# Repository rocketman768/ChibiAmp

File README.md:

# QRPAmp

A complete 10W amp for the HF bands.

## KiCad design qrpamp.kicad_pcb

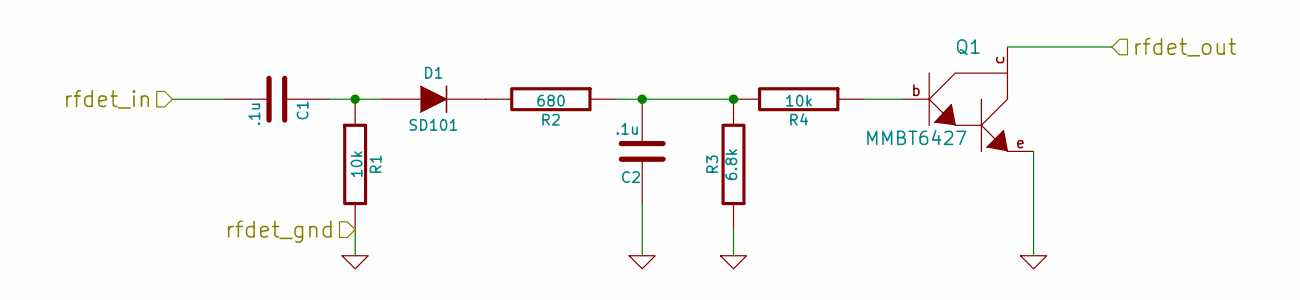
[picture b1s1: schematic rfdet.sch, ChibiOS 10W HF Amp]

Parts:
C1, C2: .1u; C_0805_HandSoldering
D1: SD101; SOD-123
Q1: MMBT6427; SOT-23-EBC_HandSoldering
R1, R4: 10k; R_1206_HandSoldering
R2: 680; R_1206_HandSoldering
R3: 6.8k; R_1206_HandSoldering

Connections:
/Microcontroller/mcu_rfdet: Q1.c; also elsewhere on the board
/RF In/Out/raw_input: C1.2; also elsewhere on the board
GND: C2.1, Q1.e, R1.2, R3.1; also elsewhere on the board
unnamed: C1.1, D1.1 (A), R1.1
unnamed: C2.2, R2.1, R3.2, R4.2
unnamed: D1.2 (K), R2.2
unnamed: Q1.b, R4.1

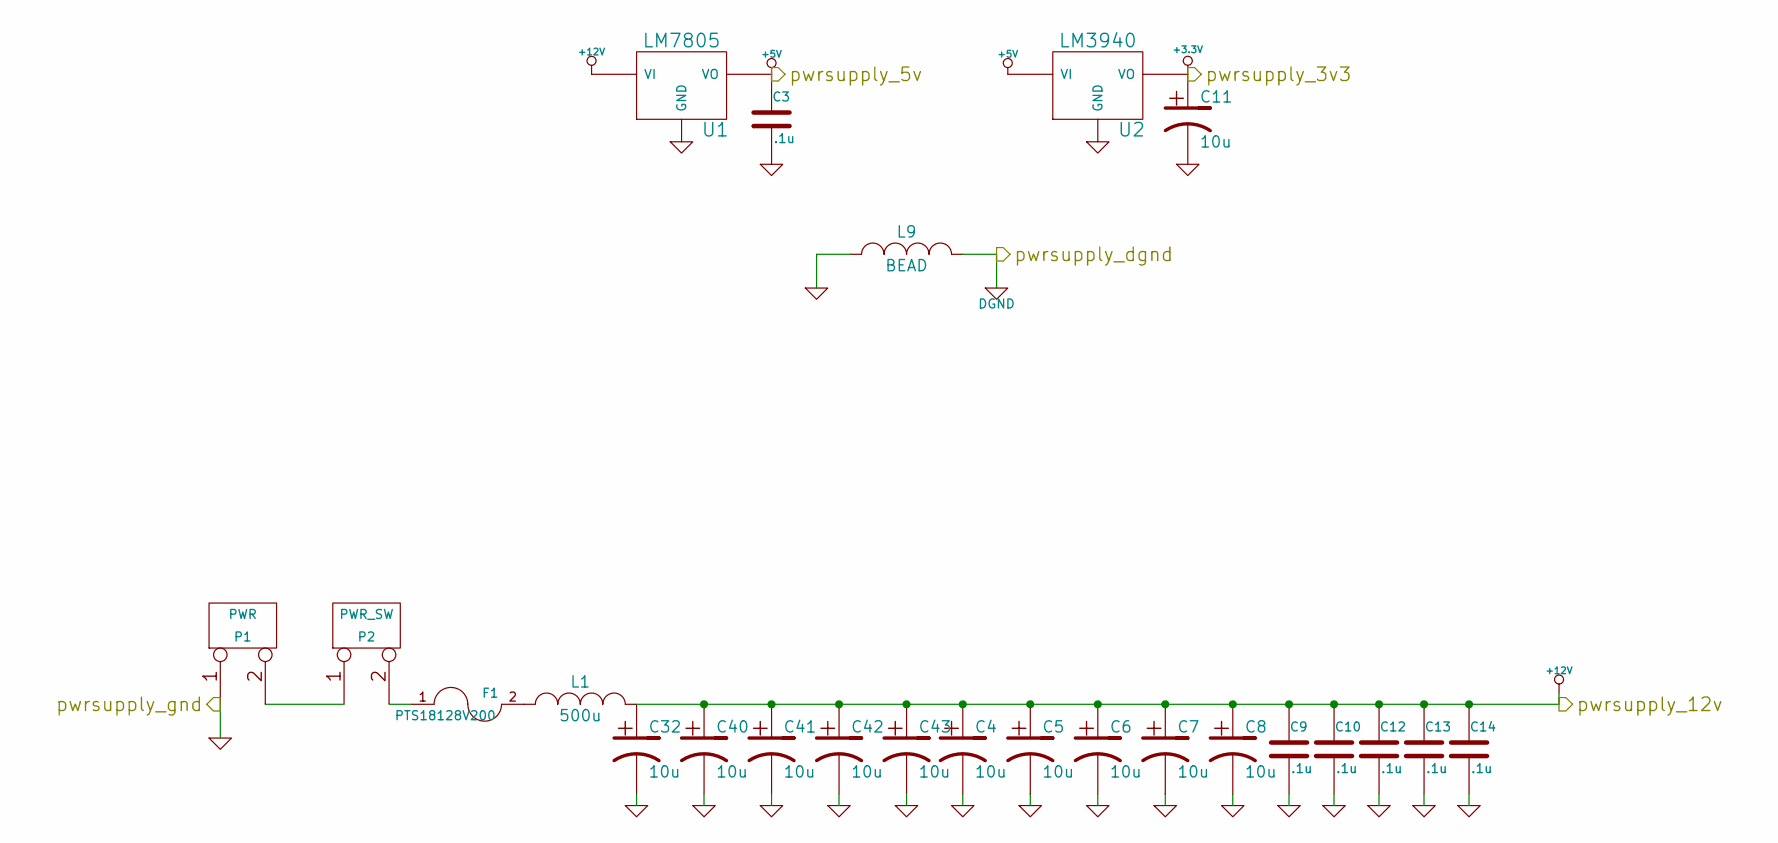
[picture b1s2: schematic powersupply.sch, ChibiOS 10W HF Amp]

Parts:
C3, C9, C10, C12, C13, C14: .1u; C_0805_HandSoldering
C4, C5, C6, C7, C8, C32, C40, C41, C42, C43: 10u; C_Radial_D5_L11_P2.5
C11: 10u; Capacitor5x11RM2.5
F1: PTS18128V200; SMD-1812_l
L1: 500u; TOROID-50
L9: BEAD; WE-SUCKW
P1: PWR; PWR2-16AWG
P2: PWR_SW; PWR2-16AWG
U1: LM7805; DPAK-3_VIVOGND
U2: LM3940; SOT-223

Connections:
+3.3V: C11.1, U2.VO; also elsewhere on the board
+5V: C3.1, U1.VO, U2.VI; also elsewhere on the board
+12V: C4.1, C5.1, C6.1, C7.1, C8.1, C9.1, C10.1, C12.1, C13.1, C14.1, C32.1, C40.1, C41.1, C42.1, C43.1, L1.2, U1.VI; also elsewhere on the board
DGND: L9.2; also elsewhere on the board
GND: C3.2, C4.2, C5.2, C6.2, C7.2, C8.2, C9.2, C10.2, C11.2, C12.2, C13.2, C14.2, C32.2, C40.2, C41.2, C42.2, C43.2, L9.1, P1.1, U1.GND, U2.GND; also elsewhere on the board
unnamed: F1.1, P2.2 (PM)
unnamed: F1.2, L1.1
unnamed: P1.2 (PM), P2.1

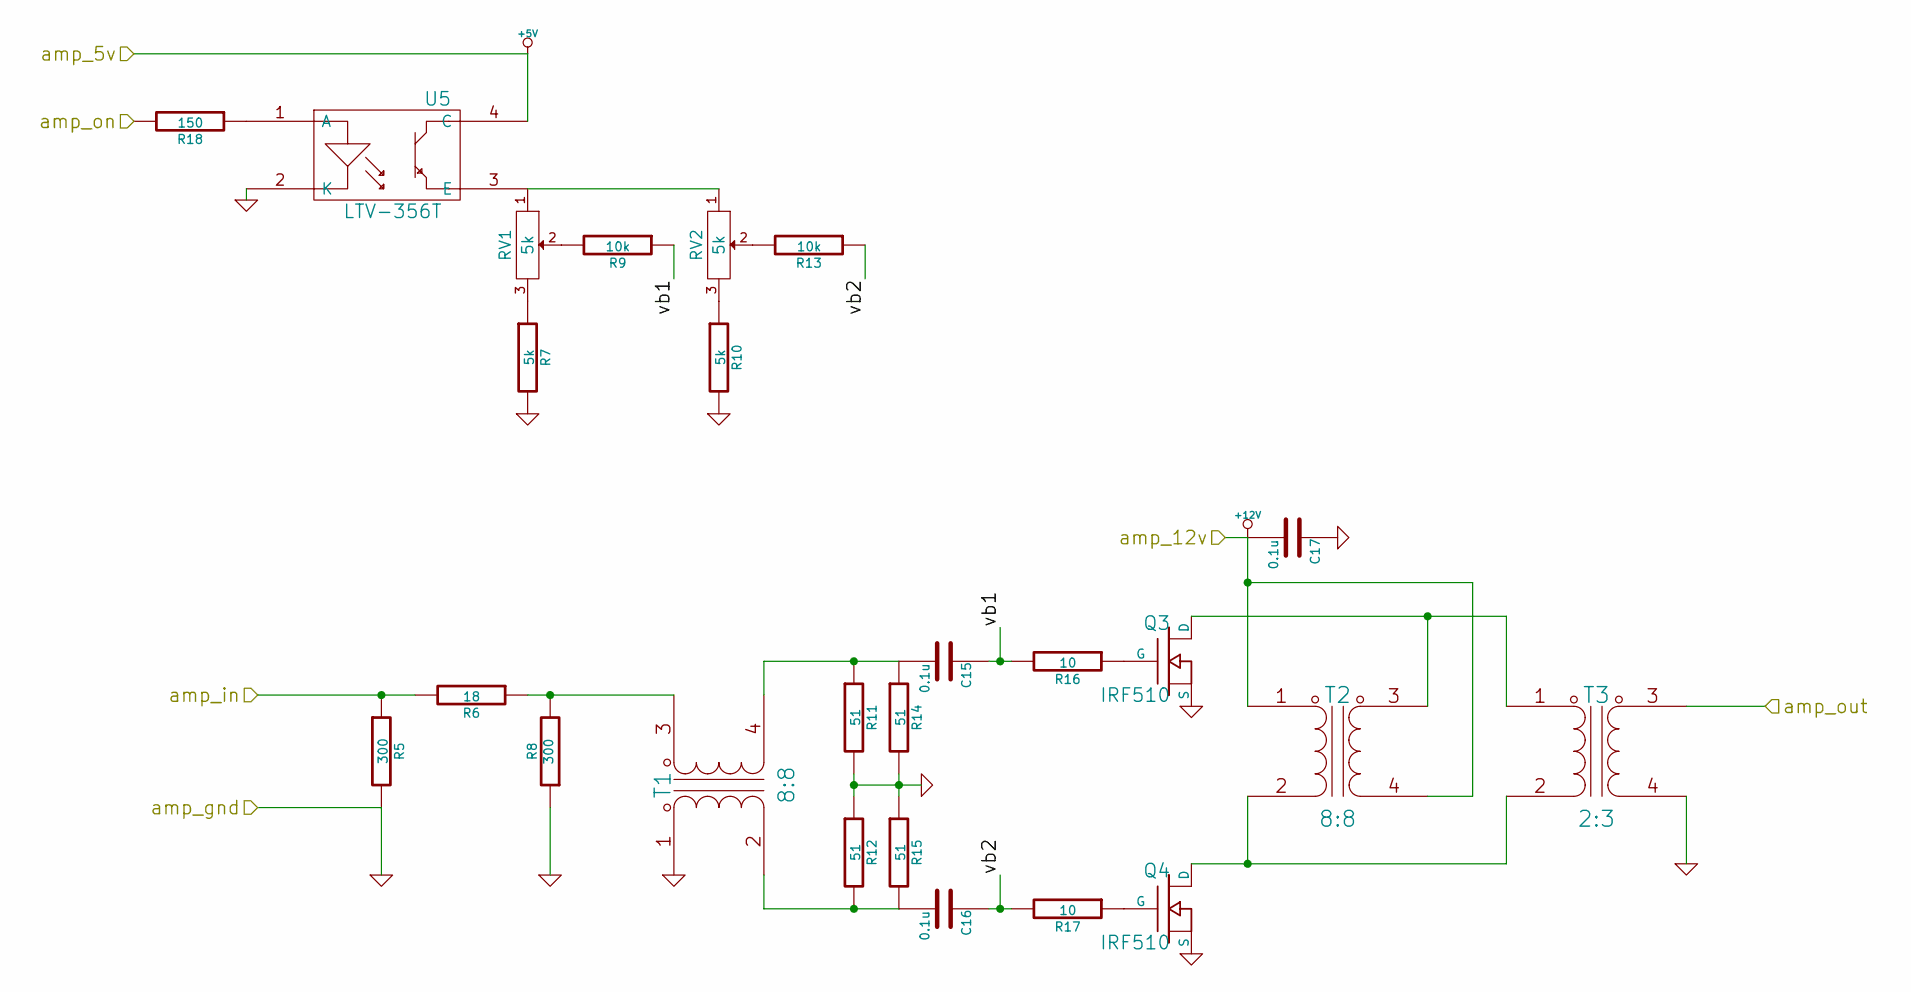
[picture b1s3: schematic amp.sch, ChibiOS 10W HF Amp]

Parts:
C15, C16, C17: 0.1u; C_0805_HandSoldering
Q3, Q4: IRF510; TO-220_FET-GDS_Horizontal_MountedFromLS_LargePads
R5, R8: 300; R1
R6: 18; R1
R7, R10: 5k; R_1206_HandSoldering
R9, R13: 10k; R_1206_HandSoldering
R11, R12, R14, R15: 51; R1
R16, R17: 10; R_1206_HandSoldering
R18: 150; R_1206_HandSoldering
RV1, RV2: 5k; Potentiometer_Trimmer_Piher_PT10_H01
T1, T2: 8:8; BN2-202
T3: 2:3; BN2-3312
U5: LTV-356T; Optocoupler_SMD_HandSoldering_KPC357_LTV35x_PC357_SingleCha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

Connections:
+5V: U5.4 (C); also elsewhere on the board
+12V: C17.2, T2.1 (PA), T2.4 (SB); also elsewhere on the board
/Amplifier/amp_in: R5.1, R6.2; also elsewhere on the board
/Amplifier/amp_on: R18.2; also elsewhere on the board
/Amplifier/amp_out: T3.3 (SA); also elsewhere on the board
/Amplifier/vb1: C15.1, R9.1, R16.2
/Amplifier/vb2: C16.1, R13.1, R17.2
GND: C17.1, Q3.S, Q4.S, R5.2, R7.2, R8.1, R10.2, R11.2, R12.1, R14.2, R15.1, T1.1 (PA), T3.4 (SB), U5.2 (K); also elsewhere on the board
unnamed: C15.2, R11.1, R14.1, T1.4 (SB)
unnamed: C16.2, R12.2, R15.2, T1.2 (PB)
unnamed: Q3.D, T2.3 (SA), T3.1 (PA)
unnamed: Q3.G, R16.1
unnamed: Q4.D, T2.2 (PB), T3.2 (PB)
unnamed: Q4.G, R17.1
unnamed: R6.1, R8.2, T1.3 (SA)
unnamed: R7.1, RV1.3
unnamed: R9.2, RV1.2
unnamed: R10.1, RV2.3
unnamed: R13.2, RV2.2
unnamed: R18.1, U5.1 (A)
unnamed: RV1.1, RV2.1, U5.3 (E)

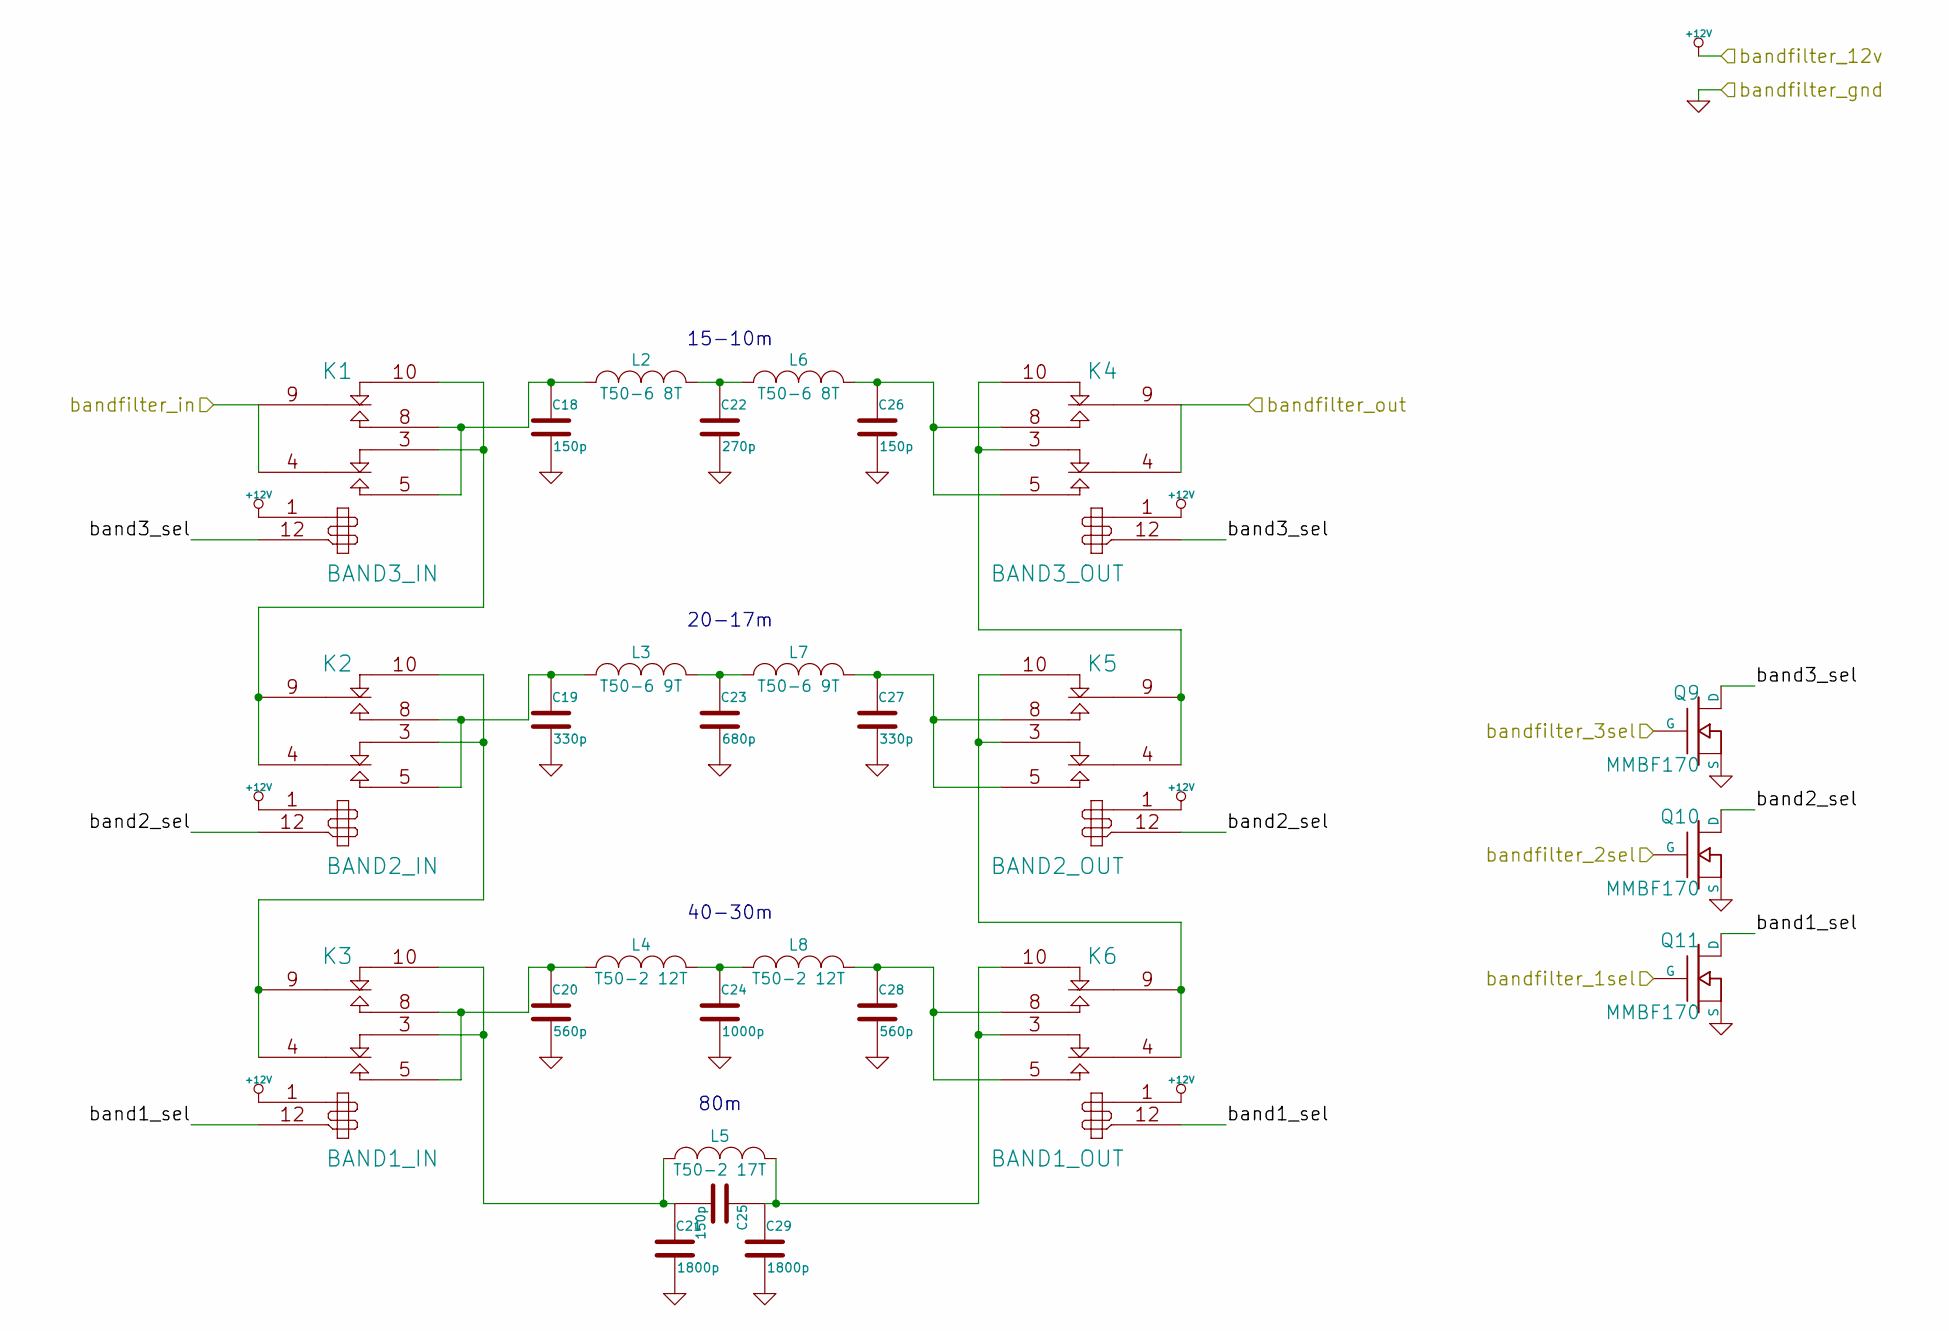
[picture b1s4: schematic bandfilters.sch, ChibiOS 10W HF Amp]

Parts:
C18, C25, C26: 150p; C1
C19, C27: 330p; C1
C20, C28: 560p; C1
C21, C29: 1800p; C1
C22: 270p; C1
C23: 680p; C1
C24: 1000p; C1
K1: BAND3_IN; EC2-12NU
K2: BAND2_IN; EC2-12NU
K3: BAND1_IN; EC2-12NU
K4: BAND3_OUT; EC2-12NU
K5: BAND2_OUT; EC2-12NU
K6: BAND1_OUT; EC2-12NU
L2, L6: T50-6 8T; TOROID-50
L3, L7: T50-6 9T; TOROID-50
L4, L8: T50-2 12T; TOROID-50
L5: T50-2 17T; TOROID-50
Q9, Q10, Q11: MMBF170; SOT-23-DGS_HandSoldering

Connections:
+12V: K1.1, K2.1, K3.1, K4.1, K5.1, K6.1; also elsewhere on the board
/Amplifier/amp_out: K1.4, K1.9; also elsewhere on the board
/Band Filters/band1_sel: K3.12, K6.12, Q11.D
/Band Filters/band2_sel: K2.12, K5.12, Q10.D
/Band Filters/band3_sel: K1.12, K4.12, Q9.D
/Band Filters/bandfilter_1sel: Q11.G; also elsewhere on the board
/Band Filters/bandfilter_2sel: Q10.G; also elsewhere on the board
/Band Filters/bandfilter_3sel: Q9.G; also elsewhere on the board
/Band Filters/bandfilter_out: K4.4, K4.9; also elsewhere on the board
GND: C18.2, C19.2, C20.2, C21.2, C22.2, C23.2, C24.2, C26.2, C27.2, C28.2, C29.2, Q9.S, Q10.S, Q11.S; also elsewhere on the board
unnamed: C18.1, K1.5, K1.8, L2.1
unnamed: C19.1, K2.5, K2.8, L3.1
unnamed: C20.1, K3.5, K3.8, L4.1
unnamed: C21.1, C25.2, K3.3 (R1), K3.10, L5.1
unnamed: C22.1, L2.2, L6.1
unnamed: C23.1, L3.2, L7.1
unnamed: C24.1, L4.2, L8.1
unnamed: C25.1, C29.1, K6.3 (R1), K6.10, L5.2
unnamed: C26.1, K4.5, K4.8, L6.2
unnamed: C27.1, K5.5, K5.8, L7.2
unnamed: C28.1, K6.5, K6.8, L8.2
unnamed: K1.3 (R1), K1.10, K2.4, K2.9
unnamed: K2.3 (R1), K2.10, K3.4, K3.9
unnamed: K4.3 (R1), K4.10, K5.4, K5.9
unnamed: K5.3 (R1), K5.10, K6.4, K6.9

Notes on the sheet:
80m
40-30m
20-17m
15-10m

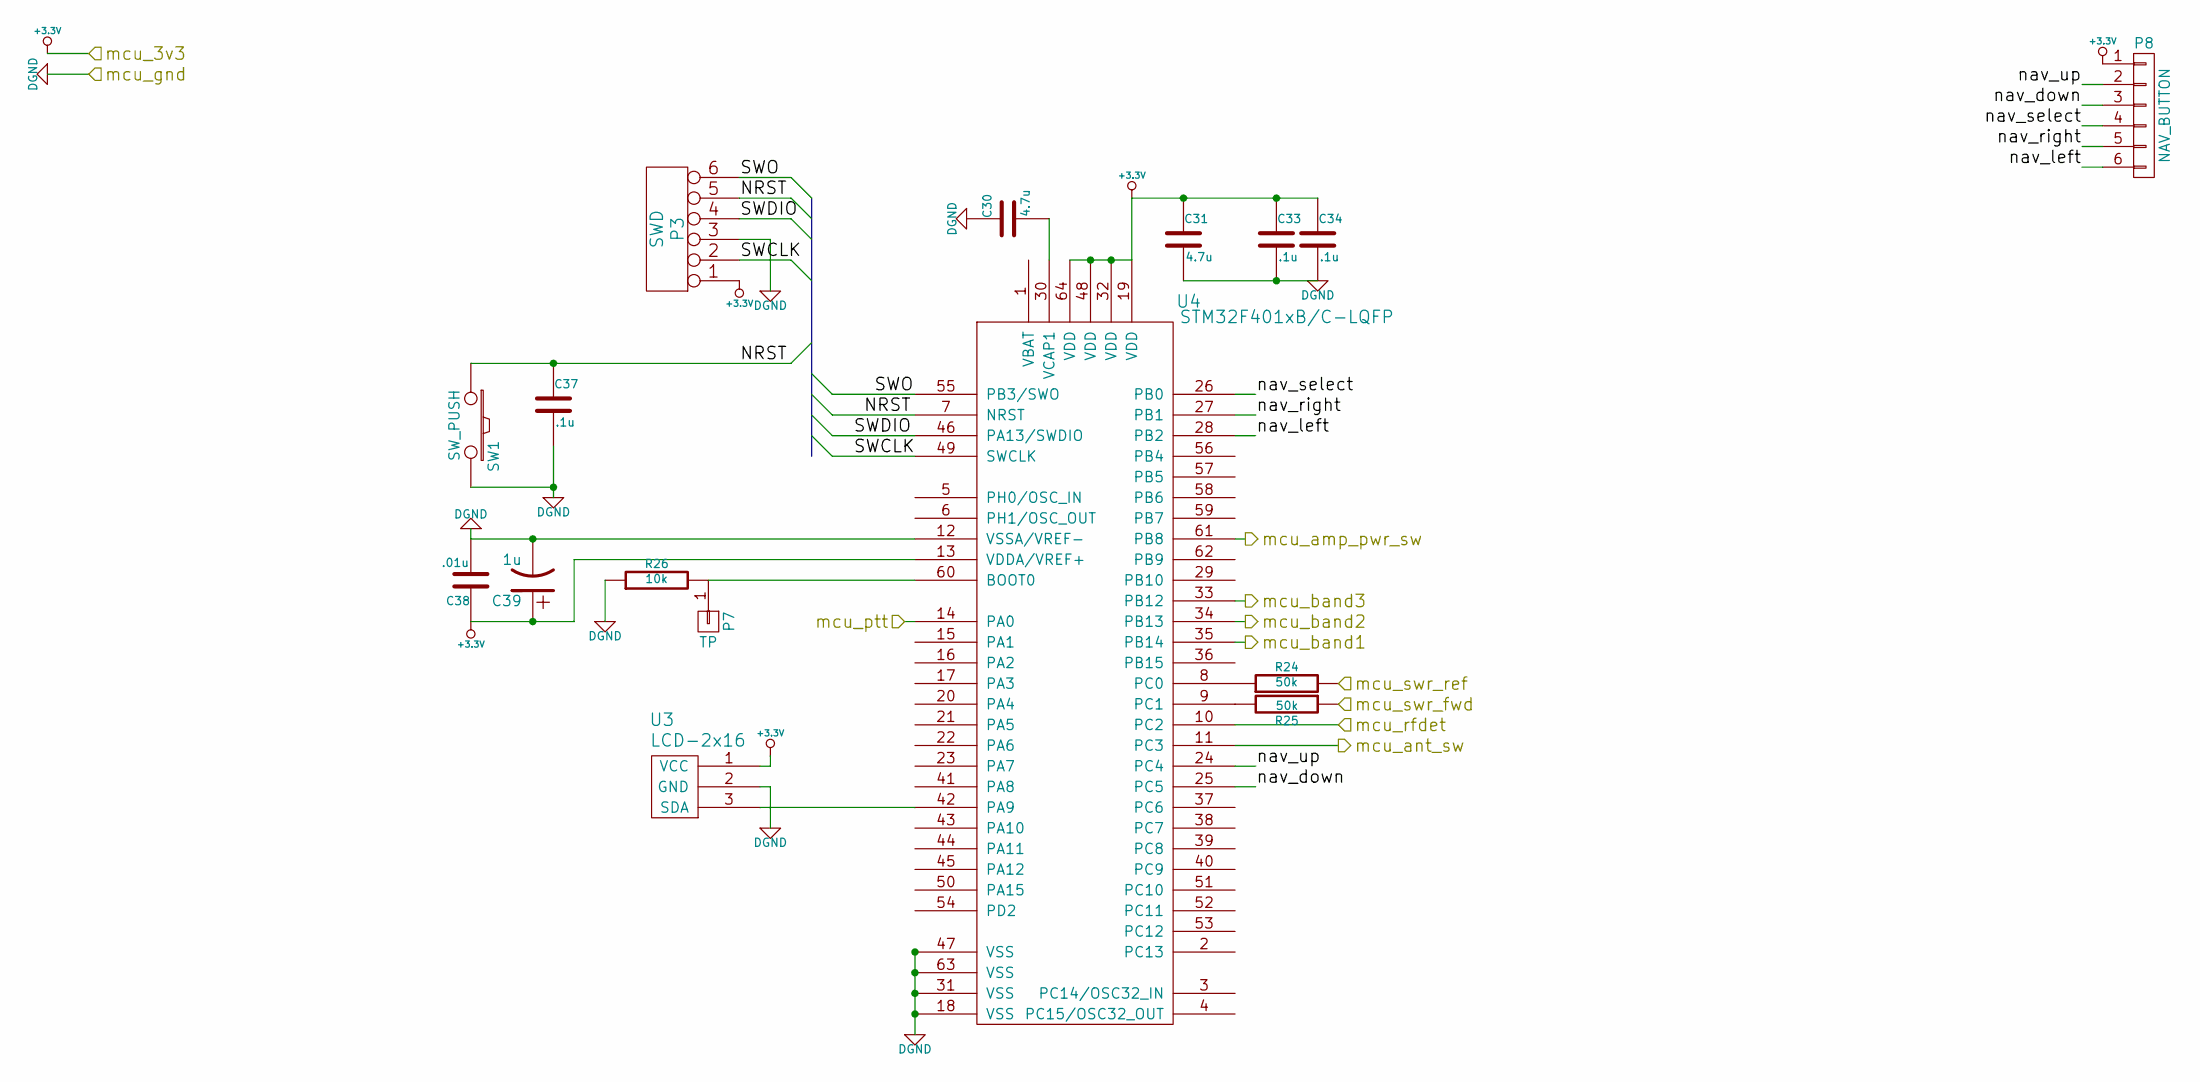
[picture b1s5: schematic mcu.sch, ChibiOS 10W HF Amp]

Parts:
C30, C31: 4.7u; C_0805_HandSoldering
C33, C34, C37: .1u; C_0805_HandSoldering
C38: .01u; C_0805_HandSoldering
C39: 1u; C_0805_HandSoldering
P3: SWD; Pin_Header_Straight_1x06
P7: TP; Measurement_Point_Round-SMD-Pad_Small
P8: NAV_BUTTON; Pin_Header_Straight_1x06
R24, R25: 50k; R_1206_HandSoldering
R26: 10k; R_1206_HandSoldering
SW1: SW_PUSH; Pin_Header_Straight_1x02
U3: LCD-2x16; Pin_Header_Straight_1x03
U4: STM32F401xB/C-LQFP; LQFP64

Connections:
+3.3V: C31.1, C33.1, C34.1, C38.1, C39.1, P3.1, P8.1, U3.1 (VCC), U4.13 (VDDA/VREF+), U4.19 (VDD), U4.32 (VDD), U4.48 (VDD), U4.64 (VDD); also elsewhere on the board
/Amplifier/amp_on: U4.61 (PB8); also elsewhere on the board
/Band Filters/bandfilter_1sel: U4.35 (PB14); also elsewhere on the board
/Band Filters/bandfilter_2sel: U4.34 (PB13); also elsewhere on the board
/Band Filters/bandfilter_3sel: U4.33 (PB12); also elsewhere on the board
/Microcontroller/NRST: C37.1, P3.5, SW1.1, U4.7 (NRST)
/Microcontroller/SWCLK: P3.2, U4.49 (SWCLK)
/Microcontroller/SWDIO: P3.4, U4.46 (PA13/SWDIO)
/Microcontroller/SWO: P3.6, U4.55 (PB3/SWO)
/Microcontroller/mcu_ptt: U4.14 (PA0); also elsewhere on the board
/Microcontroller/mcu_rfdet: U4.10 (PC2); also elsewhere on the board
/Microcontroller/mcu_swr_fwd: R25.1; also elsewhere on the board
/Microcontroller/mcu_swr_ref: R24.2; also elsewhere on the board
/Microcontroller/nav_down: P8.3, U4.25 (PC5)
/Microcontroller/nav_left: P8.6, U4.28 (PB2)
/Microcontroller/nav_right: P8.5, U4.27 (PB1)
/Microcontroller/nav_select: P8.4, U4.26 (PB0)
/Microcontroller/nav_up: P8.2, U4.24 (PC4)
/RF In/Out/ant_sw_rly: U4.11 (PC3); also elsewhere on the board
DGND: C30.1, C31.2, C33.2, C34.2, C37.2, C38.2, C39.2, P3.3, R26.1, SW1.2, U3.2 (GND), U4.12 (VSSA/VREF-), U4.18 (VSS), U4.31 (VSS), U4.47 (VSS), U4.63 (VSS); also elsewhere on the board
unnamed: C30.2, U4.30 (VCAP1)
unnamed: P7.1, R26.2, U4.60 (BOOT0)
unnamed: R24.1, U4.8 (PC0)
unnamed: R25.2, U4.9 (PC1)
unnamed: U3.3 (SDA), U4.42 (PA9)

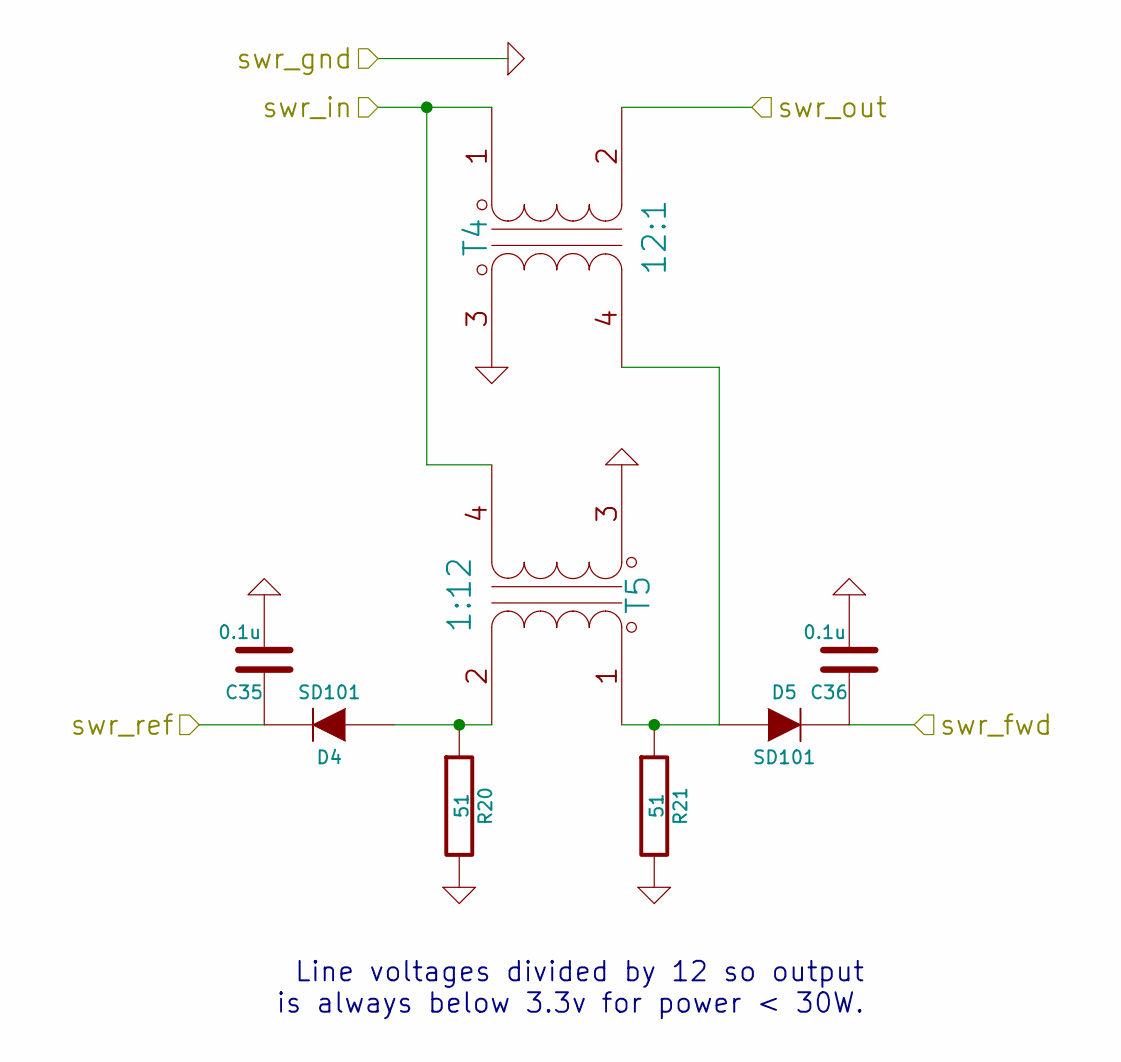
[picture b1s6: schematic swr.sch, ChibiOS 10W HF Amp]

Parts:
C35, C36: 0.1u; C_0805_HandSoldering
D4, D5: SD101; SOD-123
R20, R21: 51; R_1206_HandSoldering
T4: 12:1; TOROID2-50-singleturn
T5: 1:12; TOROID2-50-singleturn

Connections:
/Band Filters/bandfilter_out: T4.1 (PA), T5.4 (SB); also elsewhere on the board
/Microcontroller/mcu_swr_fwd: C36.1, D5.2 (K); also elsewhere on the board
/Microcontroller/mcu_swr_ref: C35.1, D4.2 (K); also elsewhere on the board
/RF In/Out/from_final: T4.2 (PB); also elsewhere on the board
GND: C35.2, C36.2, R20.2, R21.2, T4.3 (SA), T5.3 (SA); also elsewhere on the board
unnamed: D4.1 (A), R20.1, T5.2 (PB)
unnamed: D5.1 (A), R21.1, T4.4 (SB), T5.1 (PA)

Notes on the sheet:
Line voltages divided by 12 so output is always below 3.3v for power < 30W.

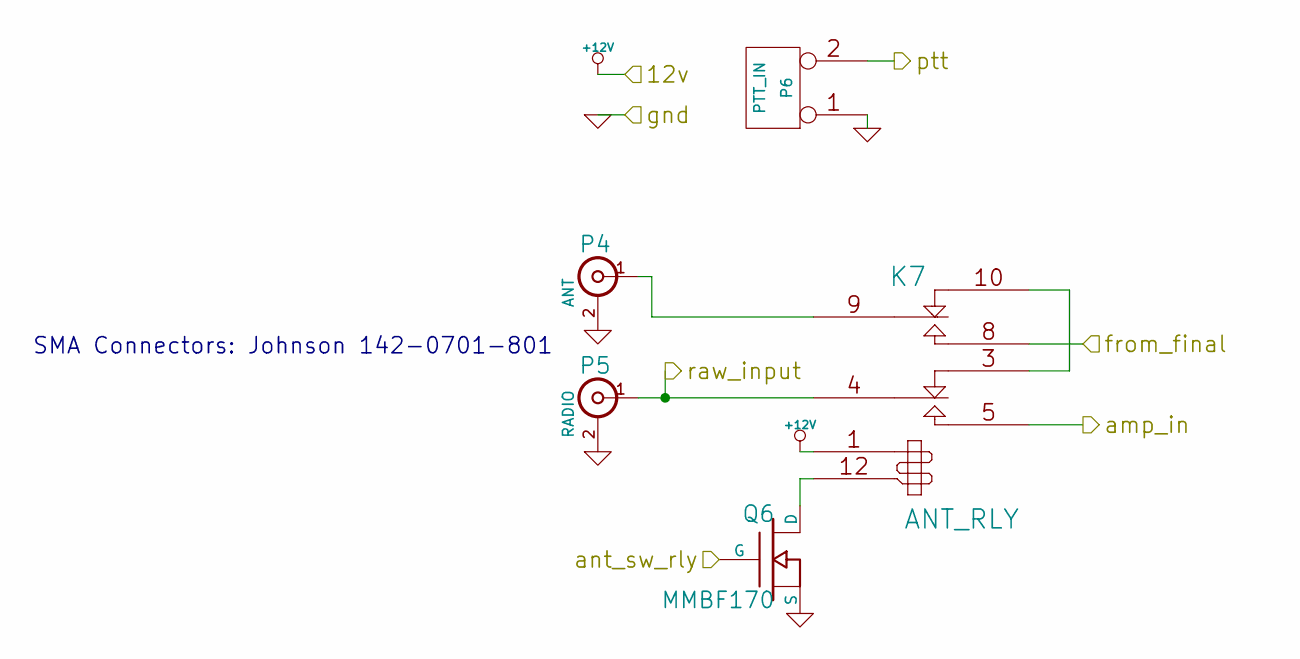
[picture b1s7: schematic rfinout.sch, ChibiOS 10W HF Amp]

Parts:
K7: ANT_RLY; EC2-12NU
P4: ANT; SMA-EDGE-0.375in
P5: RADIO; SMA-EDGE-0.375in
P6: PTT_IN; 3.5MM_SWITCHCRAFT-35RASMT2AHNTRX
Q6: MMBF170; SOT-23-DGS_HandSoldering

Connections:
+12V: K7.1; also elsewhere on the board
/Amplifier/amp_in: K7.5; also elsewhere on the board
/Microcontroller/mcu_ptt: P6.2 (PM); also elsewhere on the board
/RF In/Out/ant_sw_rly: Q6.G; also elsewhere on the board
/RF In/Out/from_final: K7.8; also elsewhere on the board
/RF In/Out/raw_input: K7.4, P5.1 (In); also elsewhere on the board
GND: P4.2 (Ext), P5.2 (Ext), P6.1, Q6.S; also elsewhere on the board
unnamed: K7.9, P4.1 (In)
unnamed: K7.3 (R1), K7.10
unnamed: K7.12, Q6.D

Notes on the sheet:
SMA Connectors: Johnson 142-0701-801

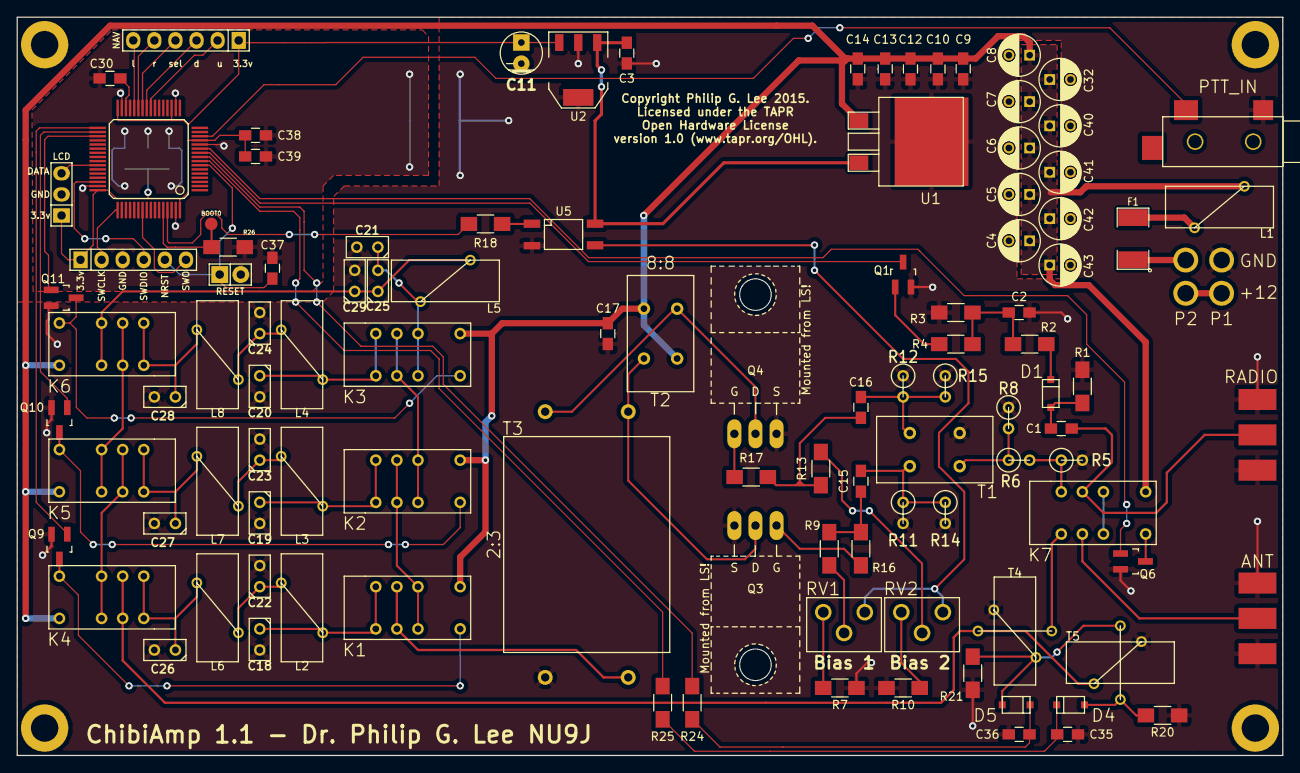
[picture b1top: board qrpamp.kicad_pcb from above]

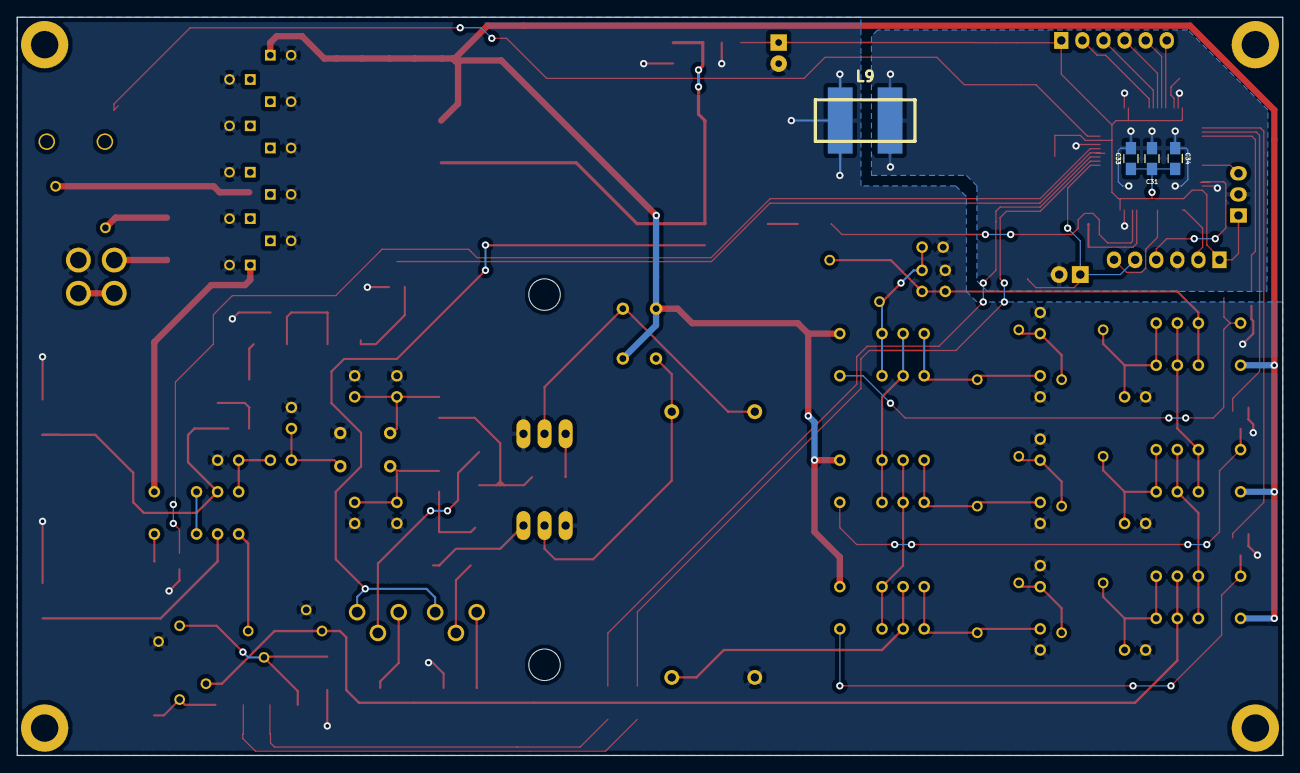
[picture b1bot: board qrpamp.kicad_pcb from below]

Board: 2 copper layers, 152.4 x 88.9 mm, 118 parts (4 on the bottom side), 78 nets.

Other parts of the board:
Mounting Hole: VAL**; MountingHole4-40
Mounting Hole#2, Mounting Hole#3, Mounting Hole#4: VAL**; MountingHole4-40

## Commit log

2014-11-27 Initial commit. Mostly-complete schematics.
2014-11-27 Added nu9j libraries to the the .pro
2014-11-27 Finished/annotated rfdet schematic
2014-11-28 Added simulation dir
    Also, due to simulation, modified the rf detector circuit
    to have higher input impdedance to distort the input rf
    less.
2014-11-28 Annotated all schematics
    - Added more caps to power supply
    - Decided on power supply fuse part
    - Changed 1n5711 SWR caps to BAT62
    - Decided on MMBF170 for amp bias switch
2014-11-28 Created netlist
2014-11-28 Added component footprint file
2014-11-28 Associated SMD resistors with 1206 footprint
2014-11-28 Pull in nu9j-footprints for LQFP64 package
2014-11-28 Associated F401 with LQFP package
2014-11-29 Associate more footprints
    - Removed flyback diodes from amp
    - Changed BAT62 -> SD101 (BAT62 is EOL)
    - Changed R and C footprints for hand-soldered versions
    - Associated through-hole cap footprints
    - Associated regulator footprints
2014-11-29 Associated transistor footprints
2014-11-29 Associated through-hole resistor footprints
2014-11-29 Finished band filters schematic
    - Associated last of the capacitors with footprints
    - Associated inductors
2014-11-30 Finished associating relays
2014-11-30 Associated ANT_RLY with footprint
2014-12-06 Everything associated except joystick
2014-12-06 Joystick is now 5-pin header and associated
    Now we are ready to lay out the board!
2014-12-06 Generated BOM
2014-12-06 Note about SMA connector part number
2014-12-06 Added pcb
2014-12-07 Fixed pin assignment issues in pcb layout
2014-12-07 Separate analog/digital gnd. Add some filtering caps and reset button.
2014-12-08 All layed out
    Several net errors fixed, and some mcu pins reassigned for better layout.
2014-12-13 Connected all mcu VSS and VDD pins.
2014-12-13 Updated nu9j-libraries for new STM401 changes
2014-12-13 Added ADC input resistors
    Also reassigned the band switch pins on the 401 for better layout.
2015-01-25 Fixed issues found with test board
    - Added MOSFETs to relay switch lines from MCU
    - Reconnected SWR in/out to actual ADC pins
    - Changed LM3940 footprint to SOT223
    - Added 4th mounting hole
    - Swapped joystick for nav button
    - Extended pads of STM32F401 for easier soldering
2015-01-25 Off to the fab!
    Had to fix an issue where the GND-DGND bead was not putting solder
    mask on the bottom pads.
2015-01-25 Hardware now under the TAPR OHL
2015-02-04 Remade BOM
2015-03-08 Put TAPR copyright notice on silkscreen
    This fixes #1. Also, change "QRPAmp" to "ChibiAmp" on front silkscreen.
2015-03-08 Fixes #5: bad bias pot pin numbers
2015-03-08 Fixes #6: removes SWR measurement voltage divider
2015-03-08 Fixes #2: Q1 pads did not match
2015-03-08 Closes #3: extend SOT23 pads
2015-03-08 Fixes #7: board to 6x3.5 inches
    Have not yet moved all the parts around.
2015-03-08 Closes #4: extend chassis pads
2015-03-08 Schematic changes to go with #3 (extending sot23 pads)
2015-07-03 Fixes #9: gate bias broken
    Replaces Q2 with LTV-356T opto-coupler between 5V and bias rail
2015-07-03 Fixes #10: resettable fuse trips too easily
    Replaced fuse with PTS18128V200 that has a hold current of 2.0A
    instead of 1.5A.
2015-07-04 Fixes #8: transistor placement
    Also, this is a major board layout change
    - Added more 12V filtering caps
    - Placed fuse in front of filtering caps
    - Changed IRF510 footprints to horizontal lower side w/ mounting hole
    - Expanded layout to fill new board size
2015-07-04 Silkscreen cleanup
2015-07-04 Fab - v1.1
    Version 1.1 is off to the fab
2015-07-04 Add copyright and license to all schematics
2015-07-04 Added a few ground vias, cleaned up some dangling tracks
2015-07-05 Put MCU decoupling caps on bottom under MCU
    This is per the design recommendations in 'PCB Design Guidelines for
    Reduced EMI' here: http://www.ti.com/lit/an/szza009/szza009.pdf
2015-07-05 Added the OSHPark renderings for the v1.0 and v1.1 boards
2015-07-06 Added gnd vias to fill in ground pours
2015-11-30 Update BOM to reflect v1.1 board
2015-11-30 Update project to kicad bzr 6336
    I guess some parts are now outdated

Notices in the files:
amp.sch:
Licensed under the TAPR Open Hardware License
Copyright 2015, Philip G. Lee
qrpamp.kicad_pcb:
Copyright Philip G. Lee 2015.
